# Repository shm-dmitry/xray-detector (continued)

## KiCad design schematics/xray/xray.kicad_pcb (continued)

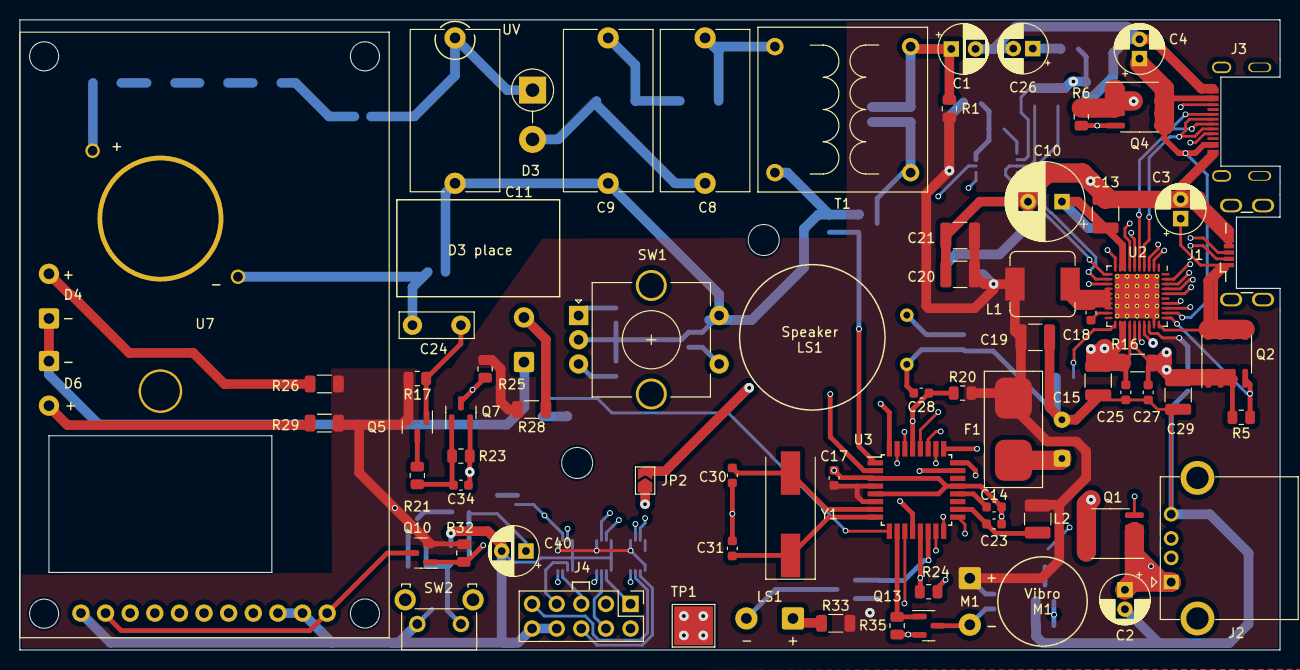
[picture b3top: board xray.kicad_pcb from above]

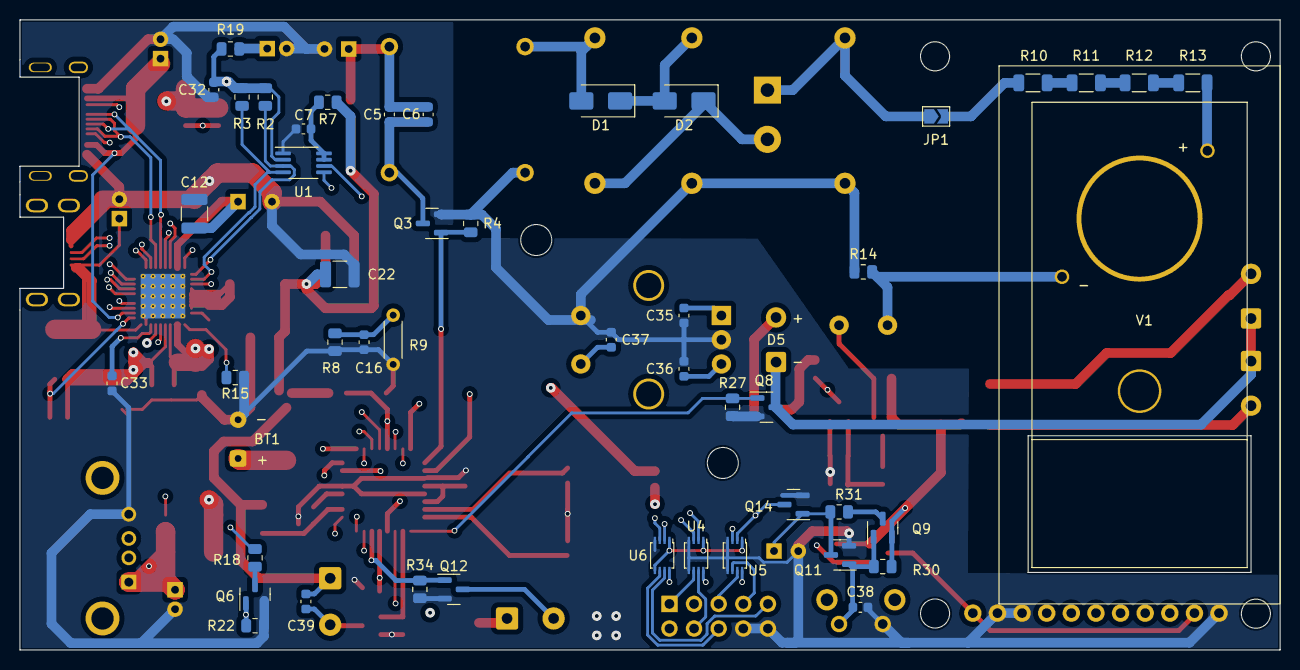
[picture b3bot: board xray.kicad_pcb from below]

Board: 4 copper layers, 130.0 x 65.0 mm, 122 parts (49 on the bottom side), 87 nets.

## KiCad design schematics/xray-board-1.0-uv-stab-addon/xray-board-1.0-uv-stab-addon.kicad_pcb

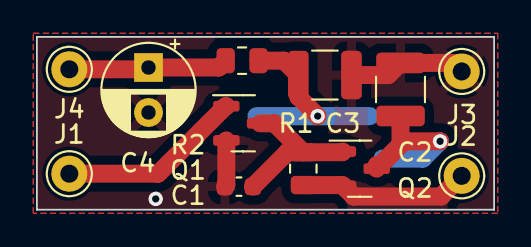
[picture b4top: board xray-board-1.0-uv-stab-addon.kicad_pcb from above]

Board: 2 copper layers, 25.4 x 9.6 mm, 13 parts (1 on the bottom side), 7 nets.

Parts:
C1: 50 nF; C_0603_1608Metric
C2, C3: 22 uF; C_1210_3225Metric
C4: 100 uF; CP_Radial_D5.0mm_P2.50mm
J1, J2, J3, J4: Conn_01x01_Pin; Pin_D1.0mm_L10.0mm
Q1: IRLML0030; SOT-23
Q2: IRLML5203; SOT-23
R1: 100K; R_0805_2012Metric
R2: 68; R_0805_2012Metric
U1: AMS1117-3.3; SOT-223-3_TabPin2

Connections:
GND: C1.2, C2.2, C3.2, C4.2, J3.1, Q1.2 (S), U1.1 (GND)
unnamed: J1.1, Q1.1 (G)
unnamed: C4.1, J4.1, R2.2
unnamed: C1.1, Q1.3 (D), Q2.1 (G), R1.2
unnamed: C2.1, Q2.3 (D), U1.3 (VI)
unnamed: C3.1, R2.1, U1.2 (VO)
VCC: J2.1, Q2.2 (S), R1.1

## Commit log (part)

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2022-12-20 debugging...
2022-12-23 continue working under firmware and schematics
2022-12-23 fixed display schematics
2022-12-26 continue working under schematics and firmware
2022-12-26 added fuse to vbat
2023-01-17 board production started
2023-04-03 Intermediate commit before re-writing ATMega and IP5328 integration
2023-04-05 Prepare to re-write UI
2023-04-07 GUI rewrited
2023-04-07 Saved 2KB PROGMEM and some RAM
2023-04-10 Prepare to rewrite display driver - remove fillCircle and fillTriangle method calls
2023-04-10 Prepare to rewrite display driver
2023-04-10 removed unused variables
2023-04-10 Rewrite colors definition
2023-04-10 UI rewrited to simplified driver. It's saves 60 bytes RAM and 7.5KB PROGMEM on simulator
2023-04-11 Re-writed driver for ST7735 display
2023-04-11 Added Dose history graph
2023-04-11 Fixed graph visualization
2023-04-11 added deleted file
2023-04-11 fixed issue with hardware display
2023-04-12 Graph visualization updated
2023-04-12 Added accumulated dose list
2023-04-14 prepare to write sleep mode
2023-04-18 UV power stabilized
2023-05-02 1. added reverrsed W2-PD(IP).v1.0 schematics. 2. minor code changes. 3. added fixme notes on schematics
2023-05-13 fixed hardware error
2023-05-14 Continue working under device - reduced one-impulse signals, fixed some hardware problems
2023-05-15 Added Betta Measurement page. Moved Impulses per UR value to the settings
2023-05-15 Fixed wrong information during startup
2023-05-15 Removed Serial from default build
2023-05-15 1. Changed one-event sound. Fixed error on settings page with cursor
2023-05-15 Fixed error with daily-accumulated dose field
2023-05-16 Start working under EXT STB
2023-05-16 EXT STB
2023-05-16 ext standby works fine
2023-05-16 1. Added auto-sleep function; 2. fixed compiler warnings
2023-05-23 preparing to print box
2023-05-26 working under box
2023-05-26 fix in box 3d model
2023-06-29 changes in 3D model
2023-08-10 v2 board - fixed errors in v1
2023-08-10 Display changed 1.8'' -> 2.2''
2023-08-10 Gerber files exported for a new display
2023-08-14 changed usb-flush schematics
2023-08-15 Board prepared to order
2023-11-20 Board v2 ordered. Preparing firmware to work with board-v2
2023-11-20 display x/y now is a 2-bytes
2023-11-22 prepare to rewrite UI
2023-11-22 Adapt UI to new screen, first version
2023-12-23 hardware works, printing box
2023-12-30 remove old 3d models
2023-12-31 updates in model and firmware
2024-01-01 fix UV generation in powersave mode
2024-01-01 try to fix HIGH VALUE in Current Accumulated Dose field
2024-01-01 fix UV in deepsleep mode
2024-01-01 fix UI issue with graph borders
2024-01-01 fix UI issue - selected item arrow centred over menu element
2024-01-01 icons increased from 8x8 to 16x16
2024-01-12 change timer impulses source in deep-sleep-mode: use T2 and disable WD to more accuacy time calculation
2024-01-18 fixed stuppid error with 'extended standby' and clock
2024-01-22 fix clock errors - at down clock works fine
2026-06-14 remove backups
2026-06-14 remove hist
2026-06-28 v3.6
